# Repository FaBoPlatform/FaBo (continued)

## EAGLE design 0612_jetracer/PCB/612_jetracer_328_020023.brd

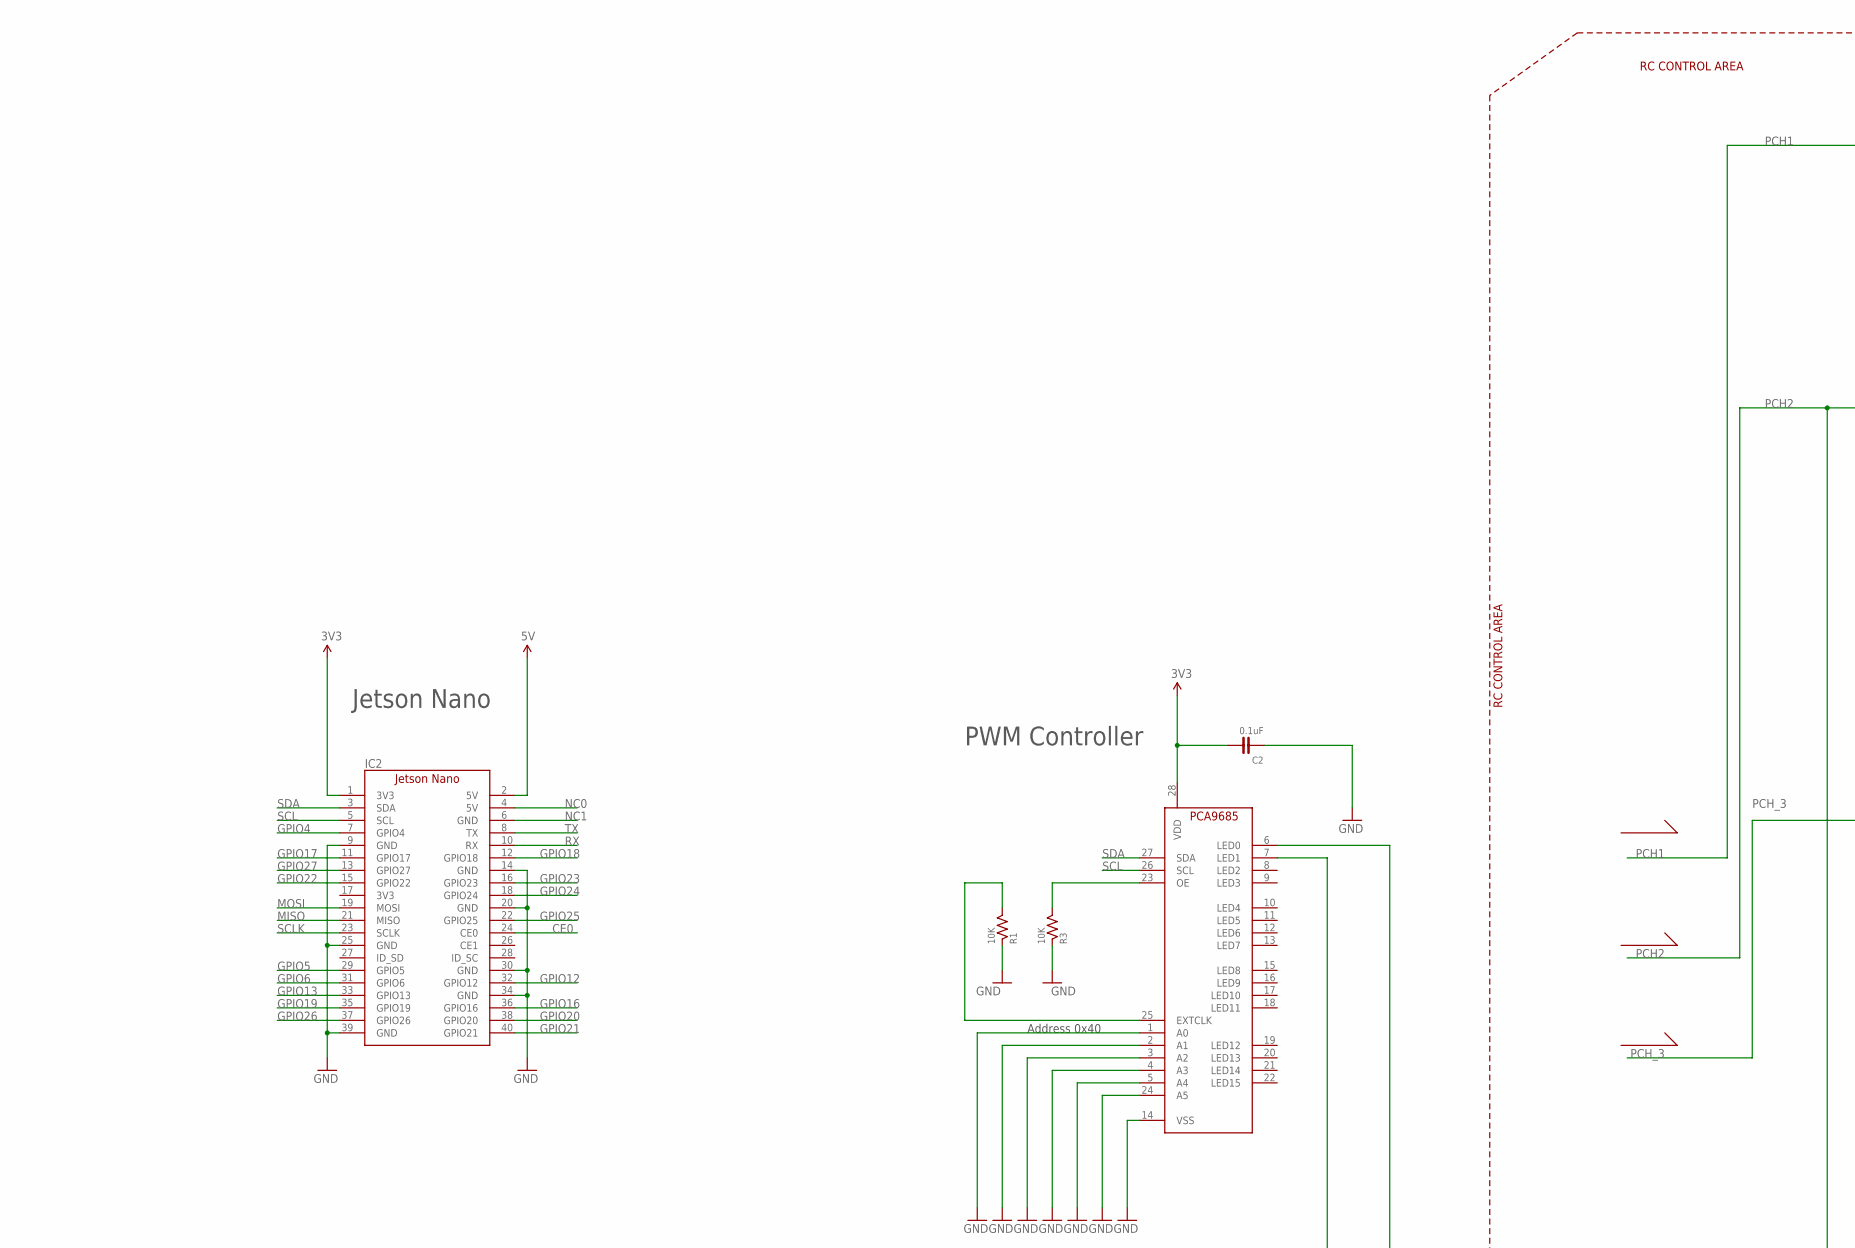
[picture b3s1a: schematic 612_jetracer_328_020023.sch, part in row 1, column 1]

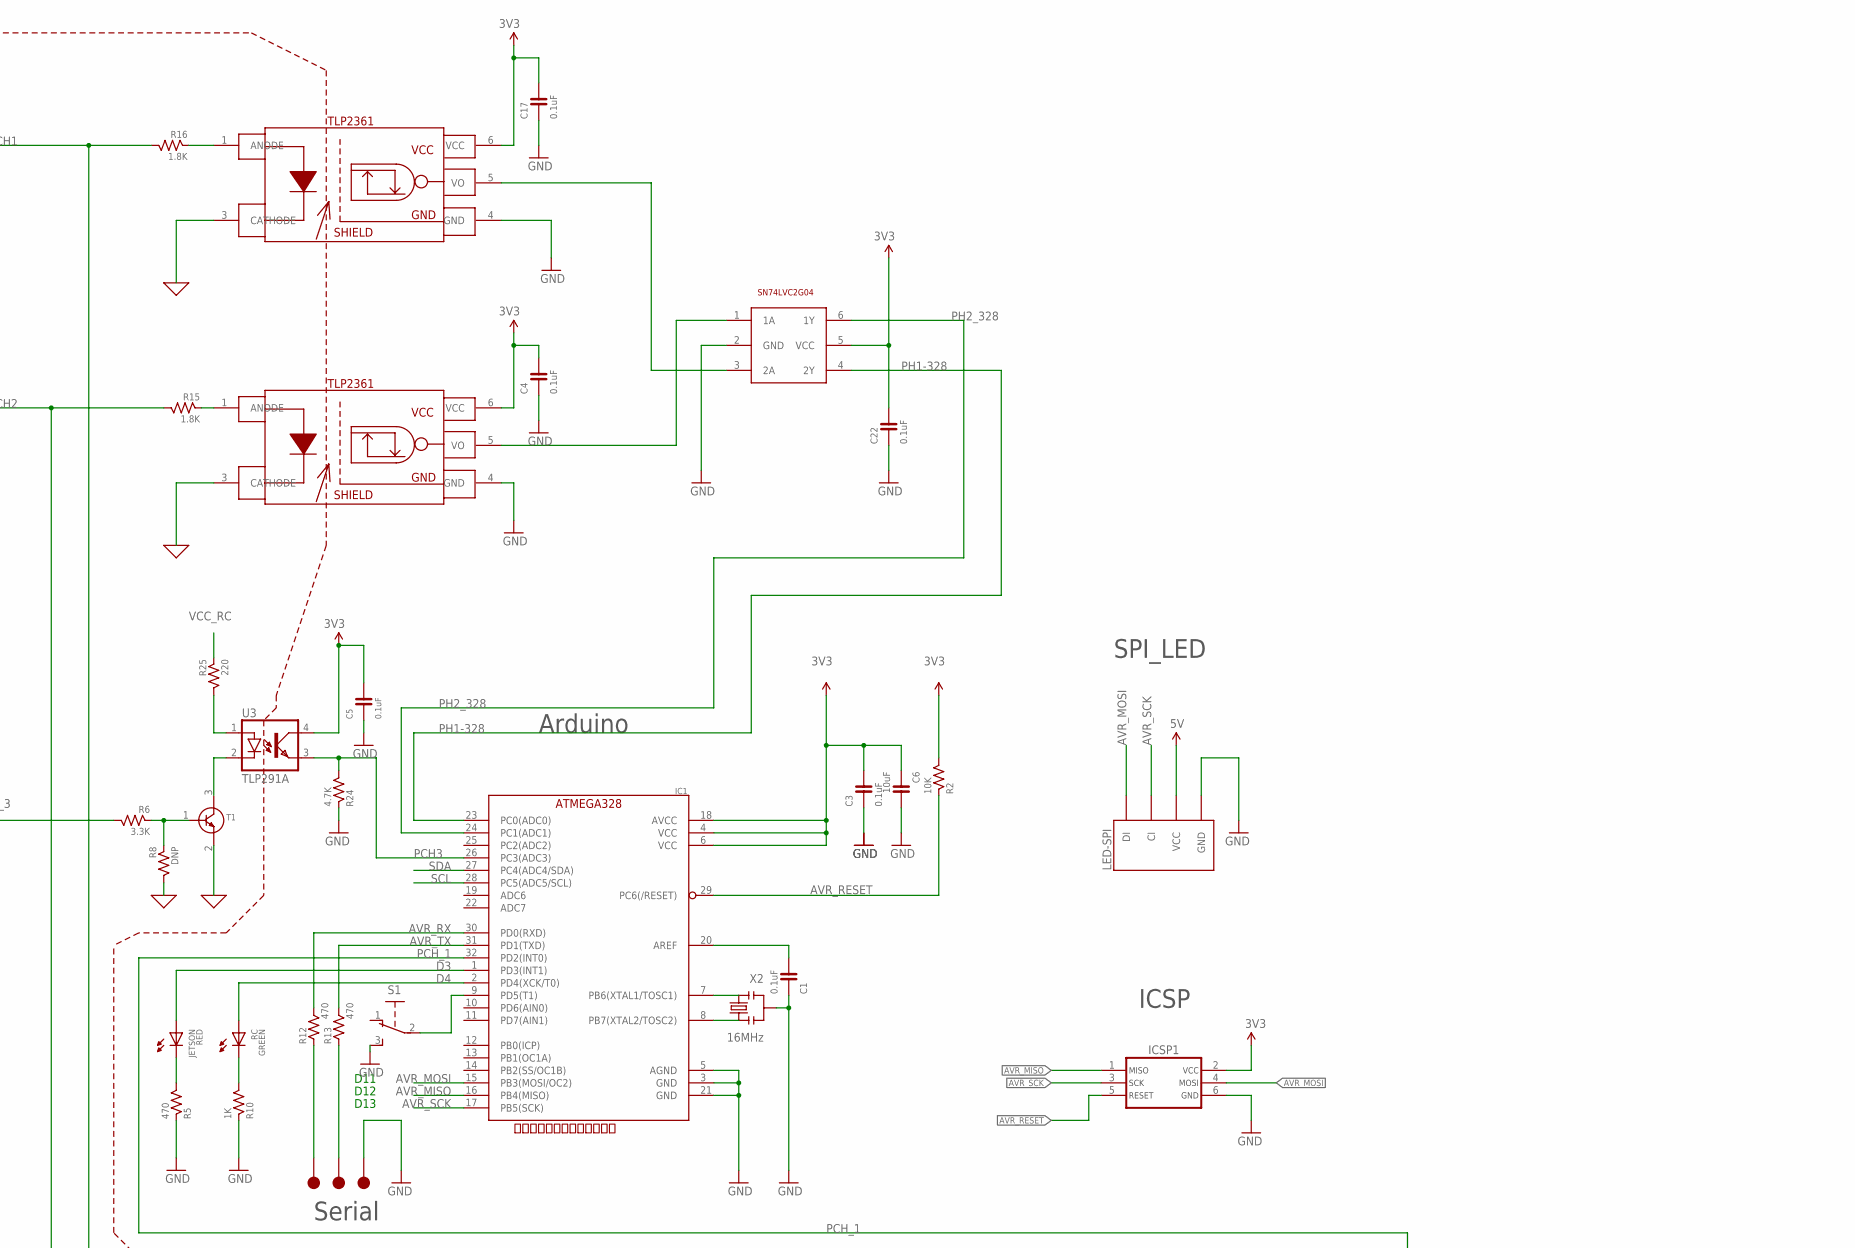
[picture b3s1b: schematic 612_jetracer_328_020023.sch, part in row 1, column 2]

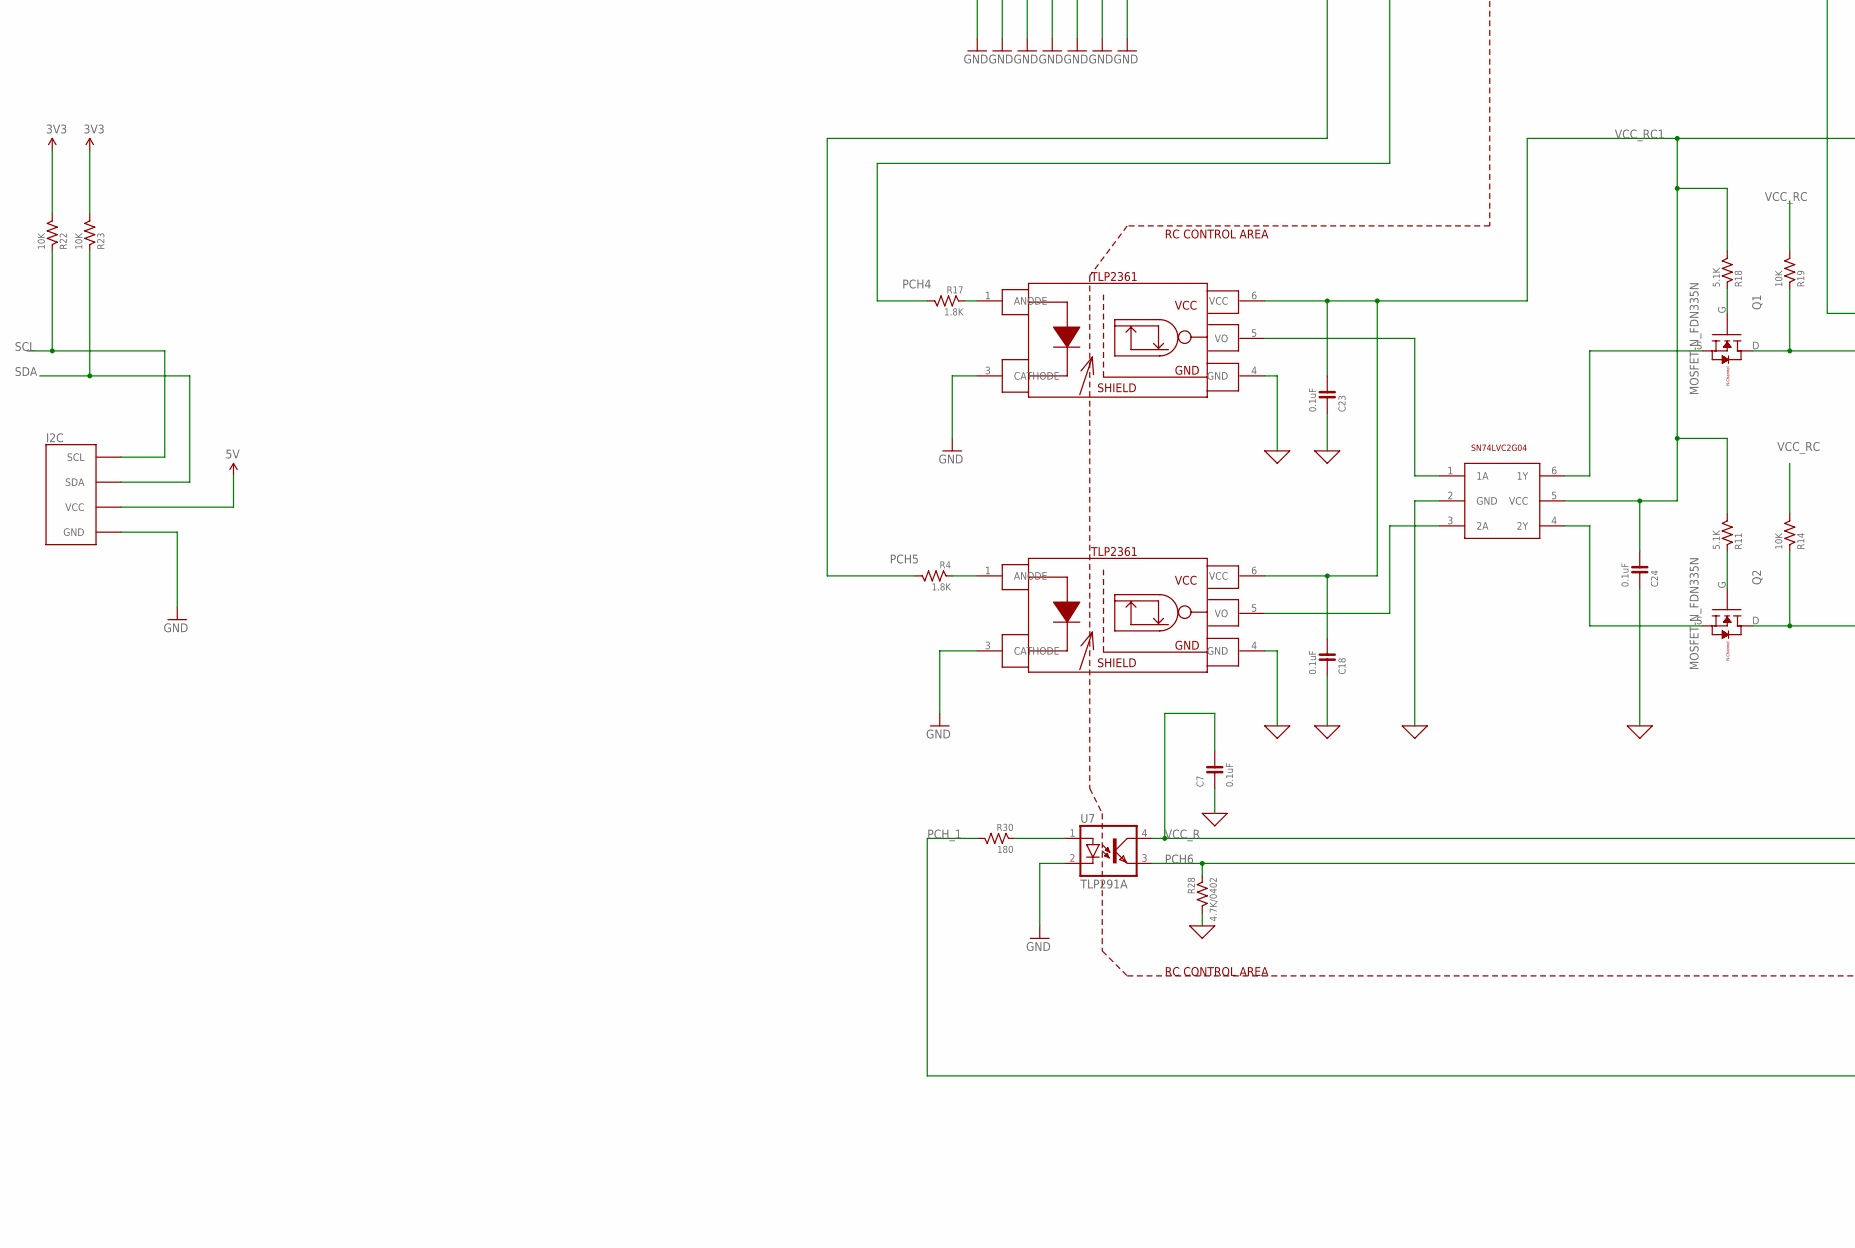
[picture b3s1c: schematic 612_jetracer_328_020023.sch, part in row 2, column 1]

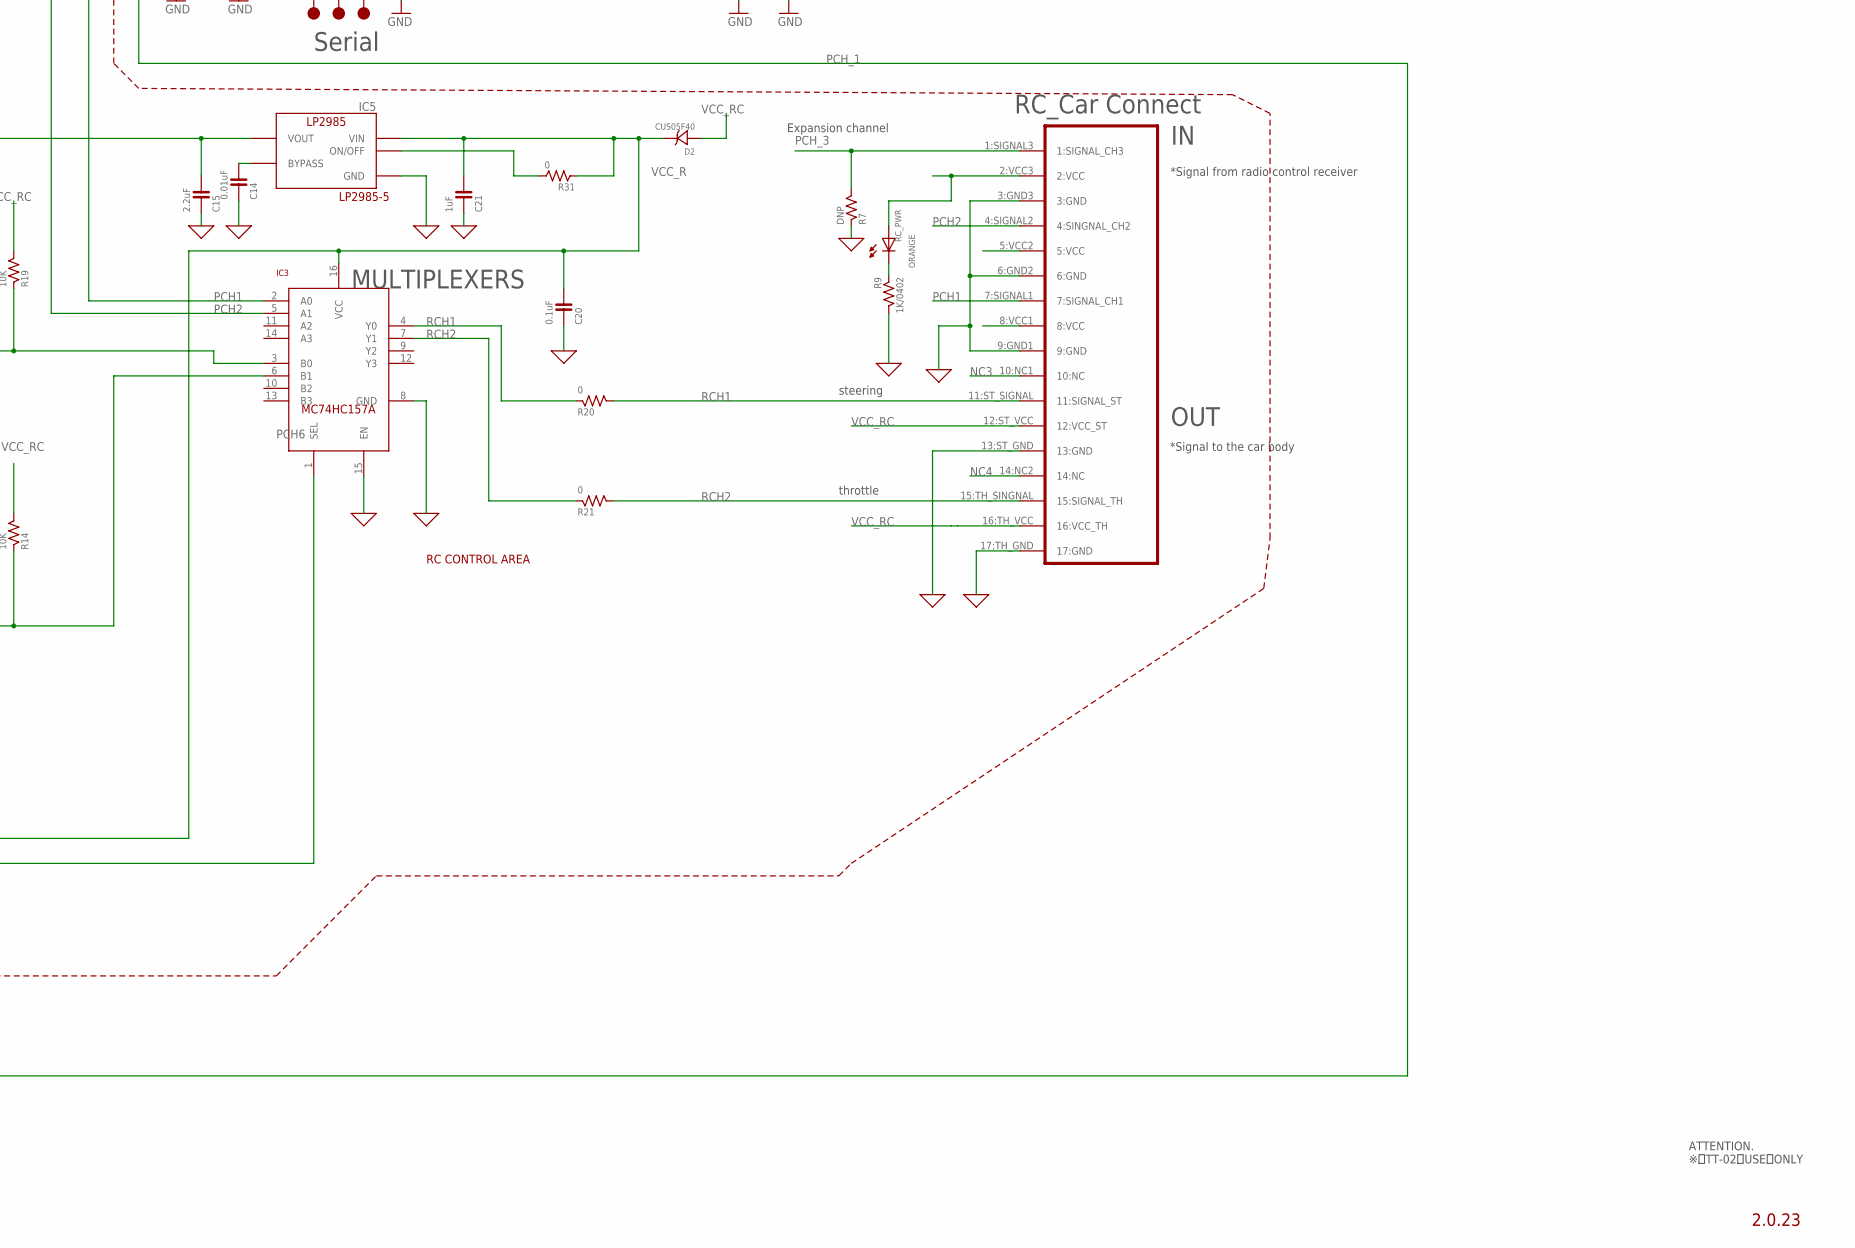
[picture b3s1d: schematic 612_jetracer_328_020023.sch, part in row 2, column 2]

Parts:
C1, C2, C5, C17, C18, C20, C23, C24: 0.1uF; 0603
C3, C4, C7, C22: 0.1uF; 0402
C6: 10uF; 0603
C14: 0.01uF; 0603
C15: 2.2uF; 0603
C21: 1uF; 0603
D2: CUS05F40
I2C: FABO-I2C_BM04B; I2C-BM04B-PASS-1
IC1: ATMEGA328P-AU; TQFP-32
IC2: JETSON_NANO_NOBORDER; JETSON_NANO_NOBOARDER
IC3: MULTIPLEXERSMC74HC157A; TSSOP-16
IC4: PCA9685_BOTTOM
IC5: LP2985-33DBV; SOT-23-5
ICSP1: ICSP_AVR-TC_NOHOLE; TC2030
JETSON: GREEN; 0603
LED-SPI: FABO-SPI-LED-BM04B; SPI-BM04B-PASS-1
Q1, Q2: MOSFET-N_FDN335N; SUPERSOT-3
R1, R2, R3, R14, R19, R22, R23: 10K; 0603
R4, R15, R16, R17: 1.8K; 0603
R5, R12, R13: 470; 0603
R6: 3.3K; 0603
R7, R8: DNP; 0603
R9: 1K/0402; 0402
R10: 1K; 0603
R11, R18: 5.1K; 0603
R20, R21, R31: 0; 0603
R24: 4.7K; 0603
R25: 220; 0603
R28: 4.7K/0402; 0402
R30: 180; 0603
RC: RED; 0603
RC_PWR: ORANGE; 0603
S1: SLIDE-SSSS810701; SSSS810701
T1: TRANSISTOR-NPN; SOT-23
T5, T6: SN74LVC2G04; SOT-23-6
TP1, TP2, TP3: TP-15
U3, U7: TLP291A; 11-3C1
U8, U9, U10, U11: TLP2361
U$1: RC_17PIN_OUTIN; PNHEADER_2.54_SMT_17PIN_RC_TT01_02
X2: 16MHz; CSTNE_V_C

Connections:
0: C7.1, C14.1, C15.1, C18.1, C20.1, C21.1, C23.1, C24.1, IC3.8 (GND), IC3.15 (EN), IC5.2 (GND), R7.1, R8.2, R9.2, R28.2, T1.2 (E), T6.2 (GND), U8.3 (CATHODE), U9.3 (CATHODE), U10.4 (GND), U11.4 (GND), U$1.3:GND3 (3:GND), U$1.6:GND2 (6:GND), U$1.9:GND1 (9:GND), U$1.13:ST_GND (13:GND), U$1.17:TH_GND (17:GND)
3V3: C2.2, C3.2, C4.2, C5.2, C6.1, C17.2, C22.2, IC1.4 (VCC), IC1.6 (VCC), IC1.18 (AVCC), IC2.1 (3V3), IC4.28 (VDD), ICSP1.2, R2.2, R22.2, R23.2, T5.5 (VCC), U3.4 (COL), U8.6 (VCC), U9.6 (VCC)
5V: I2C.5V (VCC), IC2.2 (5V), LED-SPI.5V (VCC)
AVR_MISO: IC1.16 (PB4(MISO)), ICSP1.1
AVR_MOSI: IC1.15 (PB3(MOSI/OC2)), ICSP1.4, LED-SPI.DI
AVR_RESET: IC1.29 (PC6(/RESET)), ICSP1.5, R2.1
AVR_RX: IC1.30 (PD0(RXD)), R12.2
AVR_SCK: IC1.17 (PB5(SCK)), ICSP1.3, LED-SPI.CI
AVR_TX: IC1.31 (PD1(TXD)), R13.2
CE0: IC2.24 (CE0)
D3: IC1.1 (PD3(INT1)), RC.ANODE
D4: IC1.2 (PD4(XCK/T0)), JETSON.ANODE
GND: C1.1, C2.1, C3.1, C4.1, C5.1, C6.2, C17.1, C22.1, I2C.GND, IC1.3 (GND), IC1.5 (AGND), IC1.21 (GND), IC2.9 (GND), IC2.14 (GND), IC2.20 (GND), IC2.25 (GND), IC2.30 (GND), IC2.34 (GND), IC2.39 (GND), IC4.1 (A0), IC4.2 (A1), IC4.3 (A2), IC4.4 (A3), IC4.5 (A4), IC4.14 (VSS), IC4.24 (A5), ICSP1.6, LED-SPI.GND, R1.1, R3.1, R5.1, R10.1, R24.1, S1.3, T5.2 (GND), TP3.1, U7.2 (C), U8.4 (GND), U9.4 (GND), U10.3 (CATHODE), U11.3 (CATHODE), X2.2
GPIO4: IC2.7 (GPIO4)
GPIO5: IC2.29 (GPIO5)
GPIO6: IC2.31 (GPIO6)
GPIO12: IC2.32 (GPIO12)
GPIO13: IC2.33 (GPIO13)
GPIO16: IC2.36 (GPIO16)
GPIO17: IC2.11 (GPIO17)
GPIO18: IC2.12 (GPIO18)
GPIO19: IC2.35 (GPIO19)
GPIO20: IC2.38 (GPIO20)
GPIO21: IC2.40 (GPIO21)
GPIO22: IC2.15 (GPIO22)
GPIO23: IC2.16 (GPIO23)
GPIO24: IC2.18 (GPIO24)
GPIO25: IC2.22 (GPIO25)
GPIO26: IC2.37 (GPIO26)
GPIO27: IC2.13 (GPIO27)
MISO: IC2.21 (MISO)
MOSI: IC2.19 (MOSI)
unnamed: R4.1, U11.1 (ANODE)
unnamed: IC3.3 (B0), Q1.D, R19.1
unnamed: C1.2, IC1.20 (AREF)
unnamed: IC1.8 (PB7(XTAL2/TOSC2)), X2.3
unnamed: R12.1, TP1.1
unnamed: IC4.23 (OE), R3.2
unnamed: IC4.25 (EXTCLK), R1.2
unnamed: R15.1, U9.1 (ANODE)
unnamed: T5.1 (1A), U9.5 (VO)
unnamed: T5.3 (2A), U8.5 (VO)
unnamed: R16.1, U8.1 (ANODE)
unnamed: R17.1, U10.1 (ANODE)
unnamed: T6.1 (1A), U10.5 (VO)
unnamed: IC1.7 (PB6(XTAL1/TOSC1)), X2.1
unnamed: IC1.9 (PD5(T1)), S1.2
unnamed: R13.1, TP2.1
unnamed: T6.3 (2A), U11.5 (VO)
unnamed: R5.2, RC.CATHODE
unnamed: JETSON.CATHODE, R10.2
unnamed: T1.3 (C), U3.2 (C)
unnamed: R6.1, R8.1, T1.1 (B)
unnamed: R25.2, U3.1 (A)
unnamed: R9.1, RC_PWR.CATHODE
unnamed: C14.2, IC5.4 (BYPASS)
unnamed: IC5.3 (ON/OFF), R31.2
unnamed: Q2.S, T6.4 (2Y)
unnamed: R21.2, U$1.15:TH_SINGNAL (15:SIGNAL_TH)
unnamed: R20.2, U$1.11:ST_SIGNAL (11:SIGNAL_ST)
unnamed: Q1.S, T6.6 (1Y)
unnamed: Q2.G, R11.1
unnamed: Q1.G, R18.1
unnamed: IC3.6 (B1), Q2.D, R14.1
unnamed: R30.1, U7.1 (A)
NC0: IC2.4 (5V)
NC1: IC2.6 (GND)
NC3: U$1.10:NC1 (10:NC)
NC4: U$1.14:NC2 (14:NC)
PCH1: IC3.2 (A0), R16.2, U$1.7:SIGNAL1 (7:SIGNAL_CH1)
PCH2: IC3.5 (A1), R15.2, U$1.4:SIGNAL2 (4:SINGNAL_CH2)
PCH3: IC1.26 (PC3(ADC3)), R24.2, U3.3 (EMI)
PCH4: IC4.6 (LED0), R17.2
PCH5: IC4.7 (LED1), R4.2
PCH6: IC3.1 (SEL), R28.1, U7.3 (EMI)
PCH_1: IC1.32 (PD2(INT0)), R30.2
PCH_3: R6.2, R7.2, U$1.1:SIGNAL3 (1:SIGNAL_CH3)
PH1-328: IC1.23 (PC0(ADC0)), T5.4 (2Y)
PH2_328: IC1.24 (PC1(ADC1)), T5.6 (1Y)
RCH1: IC3.4 (Y0), R20.1
RCH2: IC3.7 (Y1), R21.1
RX: IC2.10 (RX)
SCL: I2C.SCL, IC1.28 (PC5(ADC5/SCL)), IC2.5 (SCL), IC4.26 (SCL), R22.1
SCLK: IC2.23 (SCLK)
SDA: I2C.SDA, IC1.27 (PC4(ADC4/SDA)), IC2.3 (SDA), IC4.27 (SDA), R23.1
TX: IC2.8 (TX)
VCC_R: C7.2, C20.2, C21.2, D2.C (CATHODE), IC3.16 (VCC), IC5.1 (VIN), R31.1, U7.4 (COL)
VCC_RC: D2.A (ANODE), R14.2, R19.2, R25.1, RC_PWR.ANODE, U$1.2:VCC3 (2:VCC), U$1.5:VCC2 (5:VCC), U$1.8:VCC1 (8:VCC), U$1.12:ST_VCC (12:VCC_ST), U$1.16:TH_VCC (16:VCC_TH)
VCC_RC1: C15.2, C18.2, C23.2, C24.2, IC5.5 (VOUT), R11.2, R18.2, T6.5 (VCC), U10.6 (VCC), U11.6 (VCC)

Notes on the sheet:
2.0.23
Jetson Nano
PWM Controller
Address 0x40
MULTIPLEXERS
D11
D12
D13
Arduino
Serial
ICSP
*Signal from radio control receiver
*Signal to the car body
steering
throttle
Expansion channel
OUT
SPI_LED
MC74HC157A
RC CONTROL AREA
LP2985-5
ATTENTION. ※ TT-02 USE ONLY
ＡＴＭＥＧＡ３２８Ｐ－ＡＵ
RC_Car Connect

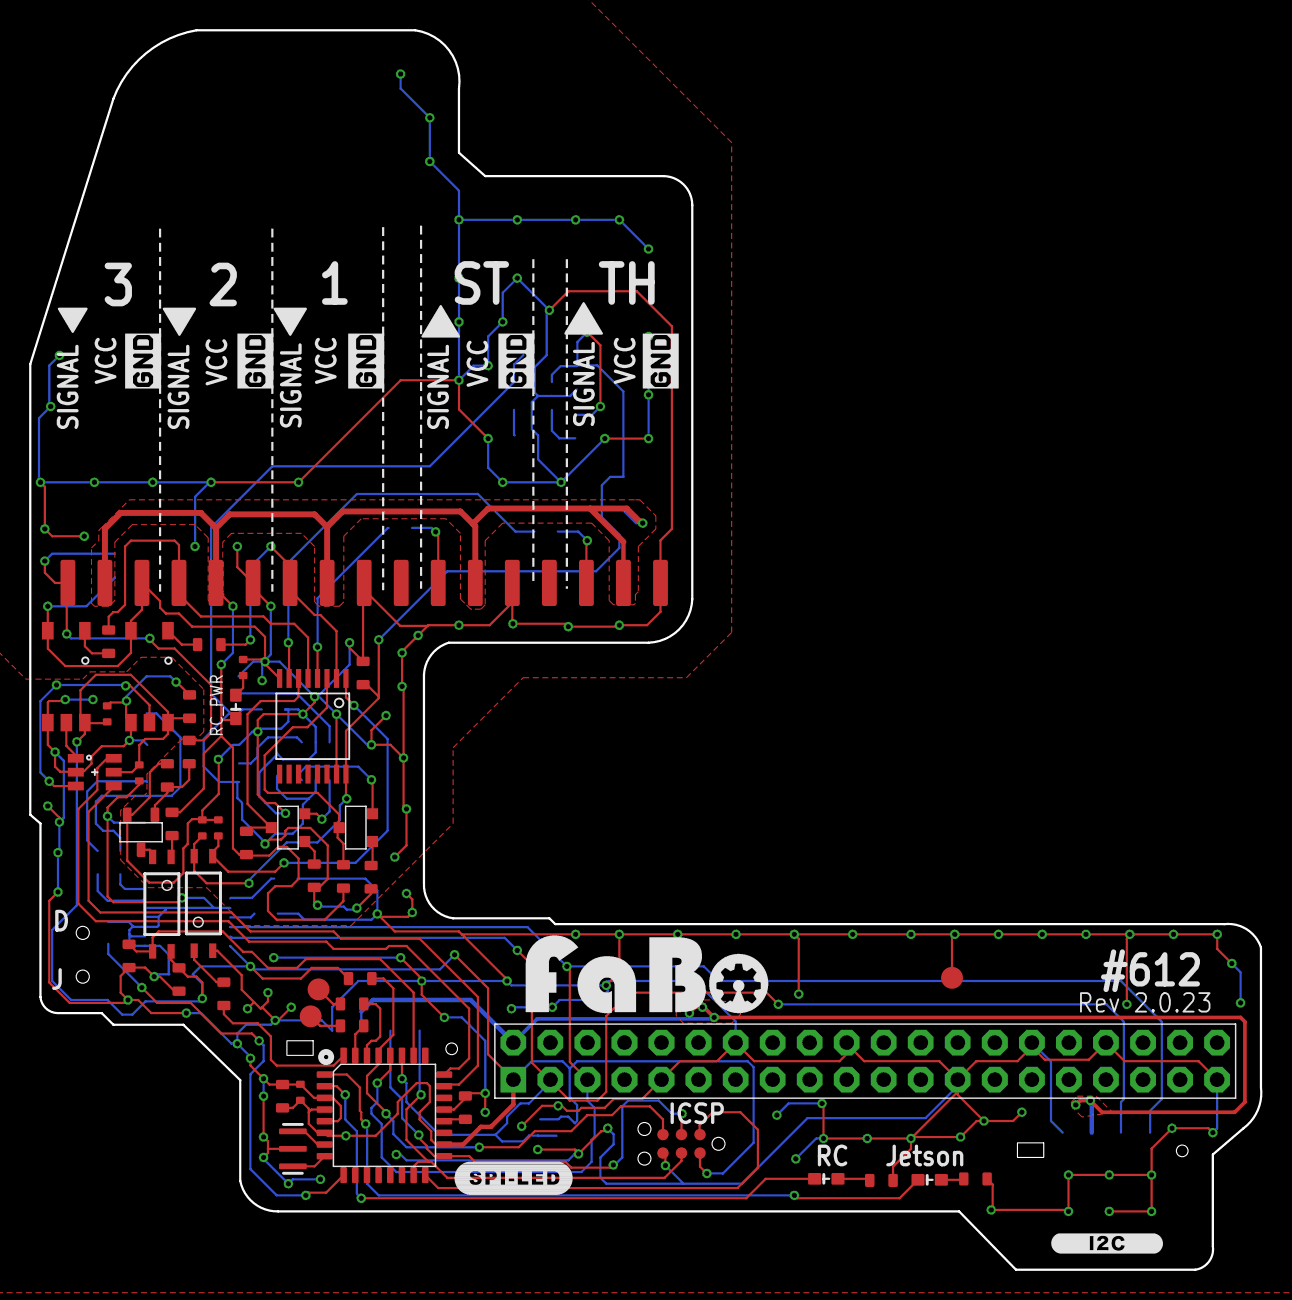
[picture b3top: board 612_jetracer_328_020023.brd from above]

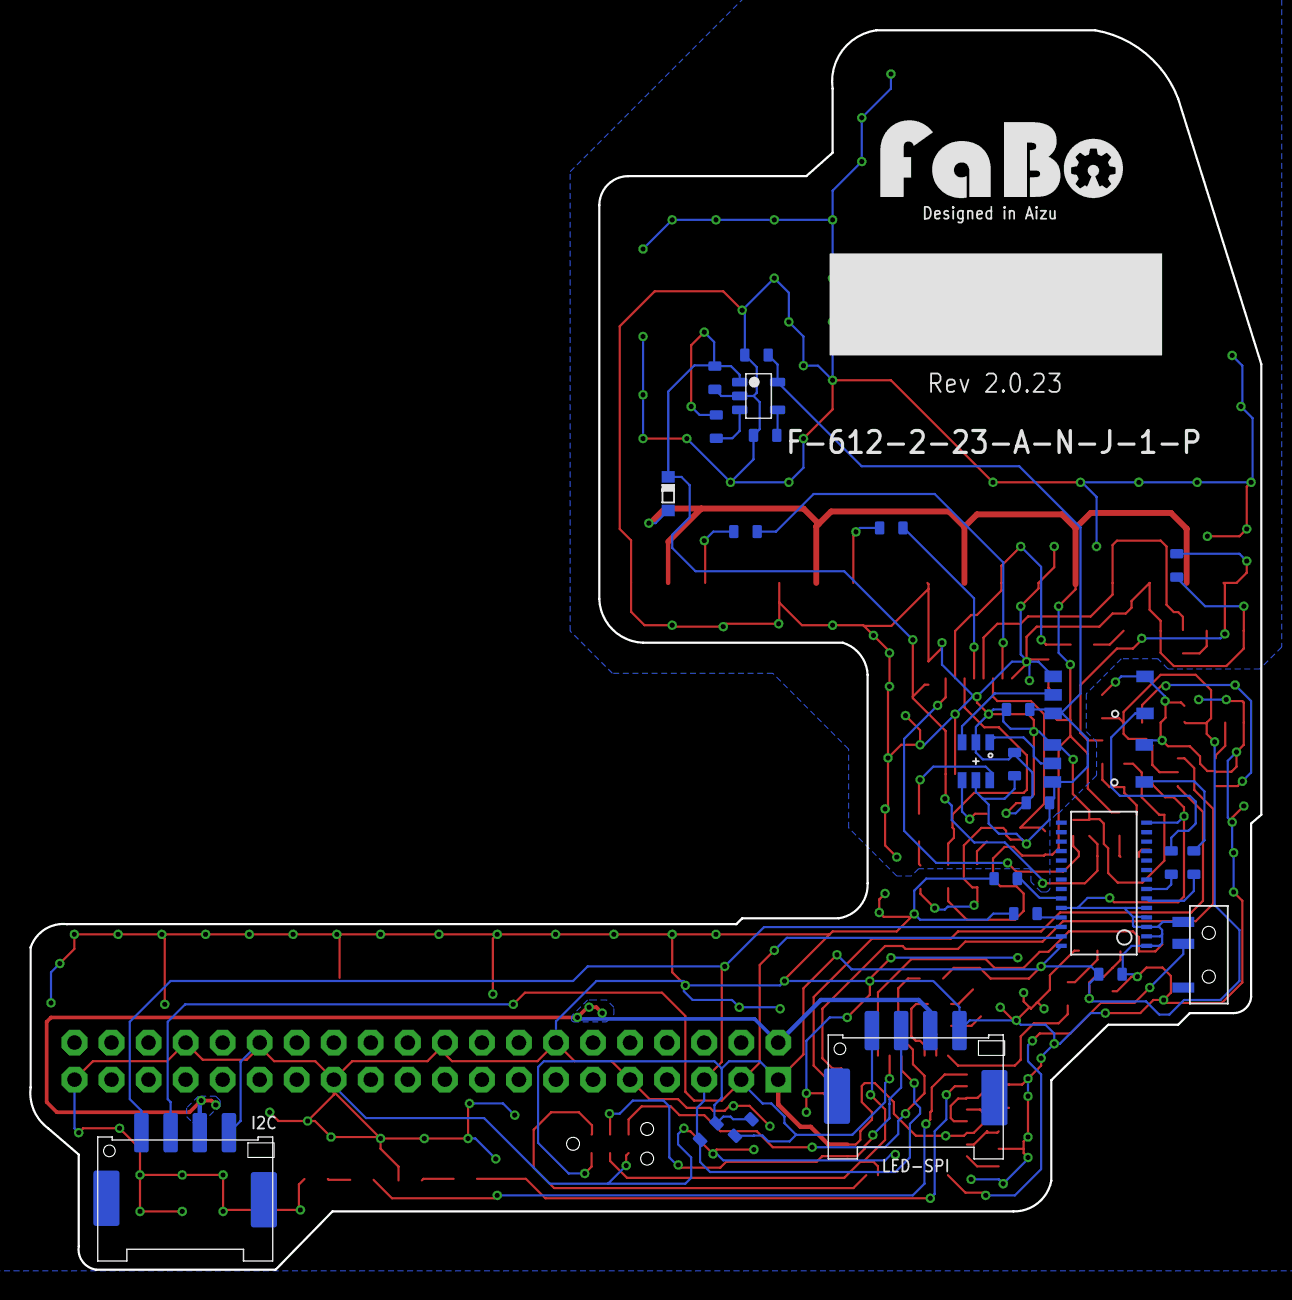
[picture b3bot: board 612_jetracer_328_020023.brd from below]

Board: 2 copper layers, 84.4 x 85.0 mm, 80 parts (26 on the bottom side), 62 nets.

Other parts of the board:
U$2, U$3: LOGO_FABO_L
U$5, U$6, U$7, U$8, U$12: LOGO_SILK_GND

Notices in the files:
parts and their libraries:
FaBo-etc: Released under the Creative Commons Attribution-ShareAlike 4.0 License
https://creativecommons.org/licenses/by-sa/4.0
